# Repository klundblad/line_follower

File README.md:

# line_follower 
A few other undergrads and I are designing an Introduction to Electrical Engineering class,
and these are some designs to minimize the size of the electronics on board of our line following robot.

PCB's for EE 299 Robot (Photo resistors and PID control):
This circuit utilizes basic, passive components to sense between light colors and dark colors in order
to follow a path marked by dark lines. Motors on the robot are tuned via PID control from four passive 
potentiometers

# V2
Adding indicators and more output power pins. Sadly I do not know how to reconfigure the 3D symbol libraries in Kicad 6.0 >:(

# V1
Very sad day when I didn't route power to any of the components on the board :(

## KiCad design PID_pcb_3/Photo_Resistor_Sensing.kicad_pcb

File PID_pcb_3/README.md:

Too many files... up to date version 5/15/22

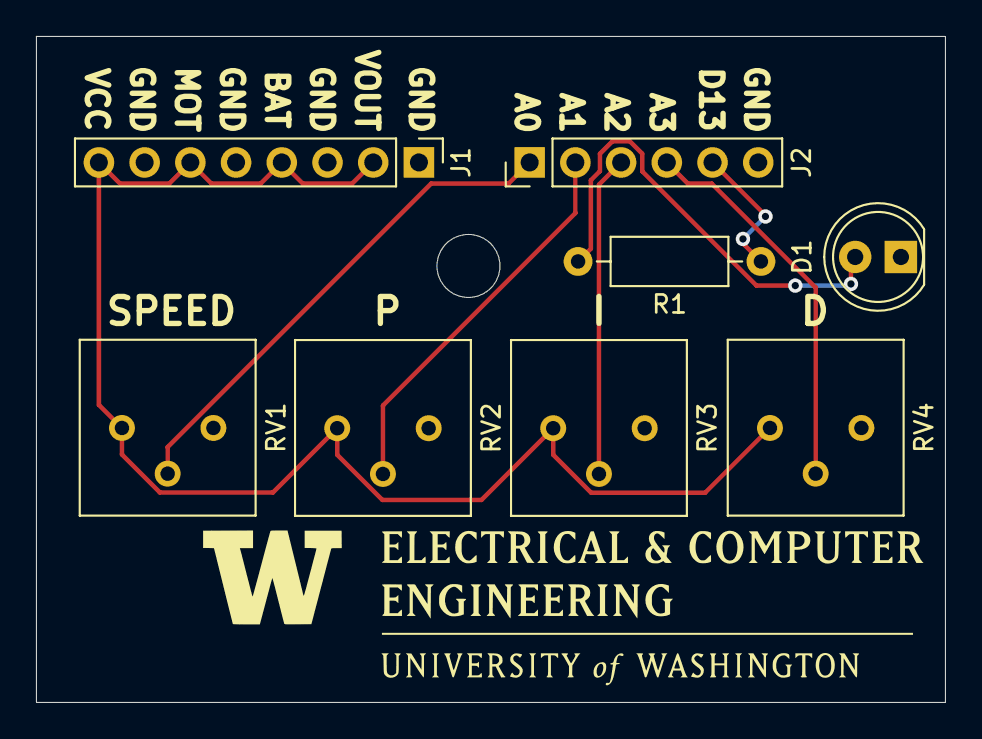
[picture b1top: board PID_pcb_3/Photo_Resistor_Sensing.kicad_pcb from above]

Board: 2 copper layers, 50.5 x 37.0 mm, 8 parts (0 on the bottom side), 8 nets.

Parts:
D1: LED; LED_D5.0mm
J1: Conn_01x08_Male; PinHeader_1x08_P2.54mm_Vertical
J2: Conn_01x06_Female; PinHeader_1x06_P2.54mm_Vertical
R1: 330; R_Axial_DIN0207_L6.3mm_D2.5mm_P10.16mm_Horizontal
RV1, RV2, RV3, RV4: 10k; Potentiometer_Bourns_3386P_Vertical

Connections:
+5V: J1.2, J1.4, J1.6, J1.8, RV1.1, RV2.1, RV3.1, RV4.1
/A0: J2.1, RV1.2
/A1: J2.2, RV2.2
/A2: J2.3, RV3.2
/A3: J2.4, RV4.2
/D13: J2.5, R1.1
GND: D1.1 (K), J1.1, J1.3, J1.5, J1.7, J2.6, RV1.3, RV2.3, RV3.3, RV4.3
unnamed: D1.2 (A), R1.2

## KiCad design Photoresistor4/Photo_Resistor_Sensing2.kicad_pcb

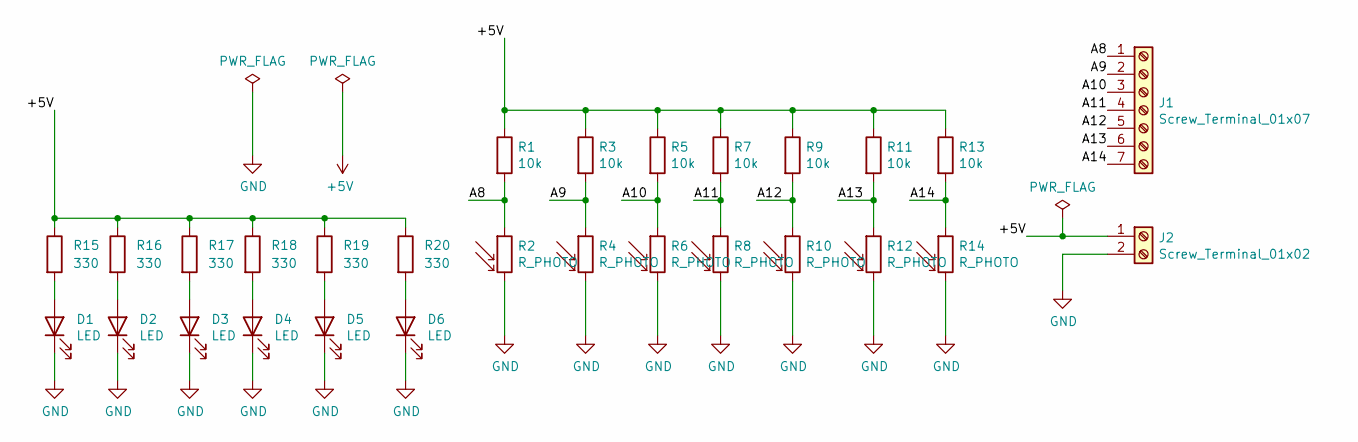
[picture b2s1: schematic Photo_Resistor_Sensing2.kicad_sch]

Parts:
D1, D2, D3, D4, D5, D6: LED; LED_D5.0mm
J1: Screw_Terminal_01x07; TerminalBlock_Phoenix_PT-1,5-7-3.5-H_1x07_P3.50mm_Horizontal
J2: Screw_Terminal_01x02; TerminalBlock_Phoenix_PT-1,5-2-3.5-H_1x02_P3.50mm_Horizontal
R1, R3, R5, R7, R9, R11, R13: 10k; R_Axial_DIN0207_L6.3mm_D2.5mm_P10.16mm_Horizontal
R2, R4, R6, R8, R10, R12, R14: R_PHOTO; R_Axial_DIN0204_L3.6mm_D1.6mm_P5.08mm_Horizontal
R15, R16, R17, R18, R19, R20: 330; R_Axial_DIN0207_L6.3mm_D2.5mm_P10.16mm_Horizontal

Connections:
+5V: J2.1, R1.1, R3.1, R5.1, R7.1, R9.1, R11.1, R13.1, R15.1, R16.1, R17.1, R18.1, R19.1, R20.1
/A8: J1.1, R1.2, R2.1
/A9: J1.2, R3.2, R4.1
/A10: J1.3, R5.2, R6.1
/A11: J1.4, R7.2, R8.1
/A12: J1.5, R9.2, R10.1
/A13: J1.6, R11.2, R12.1
/A14: J1.7, R13.2, R14.1
GND: D1.1 (K), D2.1 (K), D3.1 (K), D4.1 (K), D5.1 (K), D6.1 (K), J2.2, R2.2, R4.2, R6.2, R8.2, R10.2, R12.2, R14.2
unnamed: D1.2 (A), R15.2
unnamed: D2.2 (A), R16.2
unnamed: D3.2 (A), R17.2
unnamed: D4.2 (A), R18.2
unnamed: D5.2 (A), R19.2
unnamed: D6.2 (A), R20.2

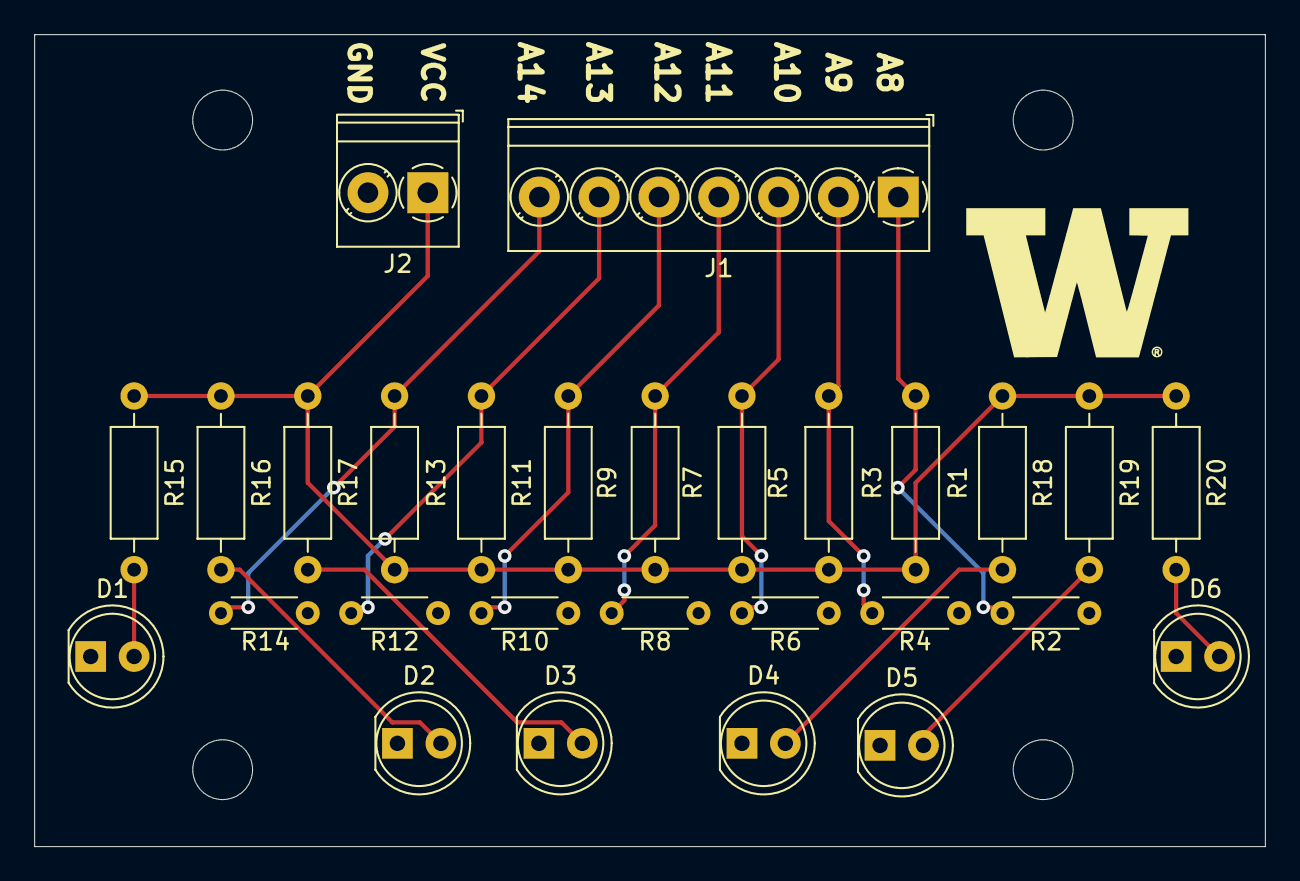
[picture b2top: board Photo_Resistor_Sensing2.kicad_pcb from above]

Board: 2 copper layers, 72.0 x 47.5 mm, 28 parts (0 on the bottom side), 15 nets.

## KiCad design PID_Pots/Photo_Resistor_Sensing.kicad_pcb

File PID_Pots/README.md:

# Potentiometers for PID control
This circuit has four trimmed potentiometers that can be tuned, connected to headers to send tuned voltages to the analog pins of the arduino mega

# GerberFiles
These are files ready to be fabricated into a printed circuit board for this circuit, if ordering from JLCPCB, compress this folder and upload directly

# Schematic and Layout Reference

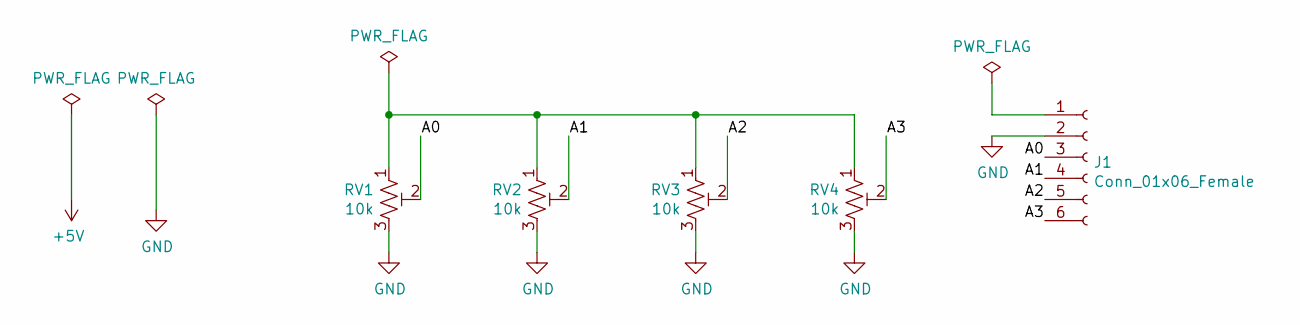
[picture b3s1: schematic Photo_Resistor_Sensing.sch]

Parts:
J1: Conn_01x06_Female; PinHeader_1x06_P2.54mm_Vertical
RV1, RV2, RV3, RV4: 10k; Potentiometer_Bourns_3386P_Vertical

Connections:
/A0: J1.3, RV1.2
/A1: J1.4, RV2.2
/A2: J1.5, RV3.2
/A3: J1.6, RV4.2
GND: J1.2, RV1.3, RV2.3, RV3.3, RV4.3
unnamed: RV1.1, RV2.1, RV3.1, RV4.1

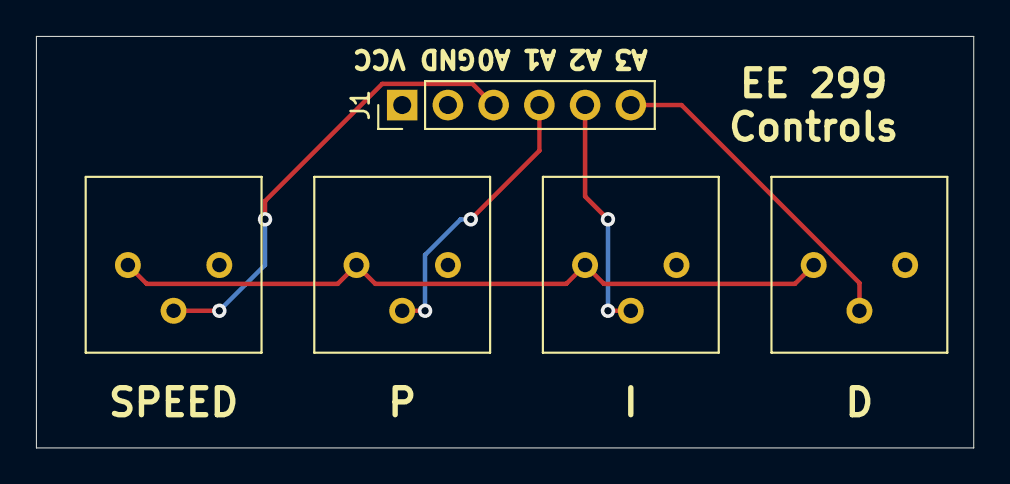
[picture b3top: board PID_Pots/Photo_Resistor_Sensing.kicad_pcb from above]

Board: 2 copper layers, 52.1 x 22.9 mm, 5 parts (0 on the bottom side), 6 nets.

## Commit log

2022-05-01 I am a clown
2022-05-01 Fixed schematic, added new components
